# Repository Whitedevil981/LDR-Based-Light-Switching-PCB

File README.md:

# LDR-Based-Light-Switching-PCB
# Project Objective:
To design a light control system that automatically turns on a street light (or any light source) when it becomes dark and turns it off when there is sufficient daylight, using an LDR (Light Dependent Resistor) and basic electronic components.
# Working Principle:
The system is based on the light-sensing capability of an LDR. An LDR changes its resistance based on the intensity of light falling on it:

Bright light = low resistance

Darkness = high resistance

This change in resistance alters the voltage in a voltage divider circuit, which is used to switch a transistor. The transistor acts as an electronic switch to turn a relay or LED on or off.
# What the Basic PBC Circuit Includes:

LDR as light sensor

NPN Transistor 

LED/light bulb

Resistors 

Power supply (Battery)

# How It Works:
In daylight, the LDR has low resistance, so the transistor stays OFF → light/bulb is OFF.

At night or in darkness, LDR resistance increases, providing a base current to the transistor.

Transistor turns ON, activating the relay (or lighting up an LED/bulb).

The light remains ON until daylight is detected again.

# Applications:

Street lighting automation

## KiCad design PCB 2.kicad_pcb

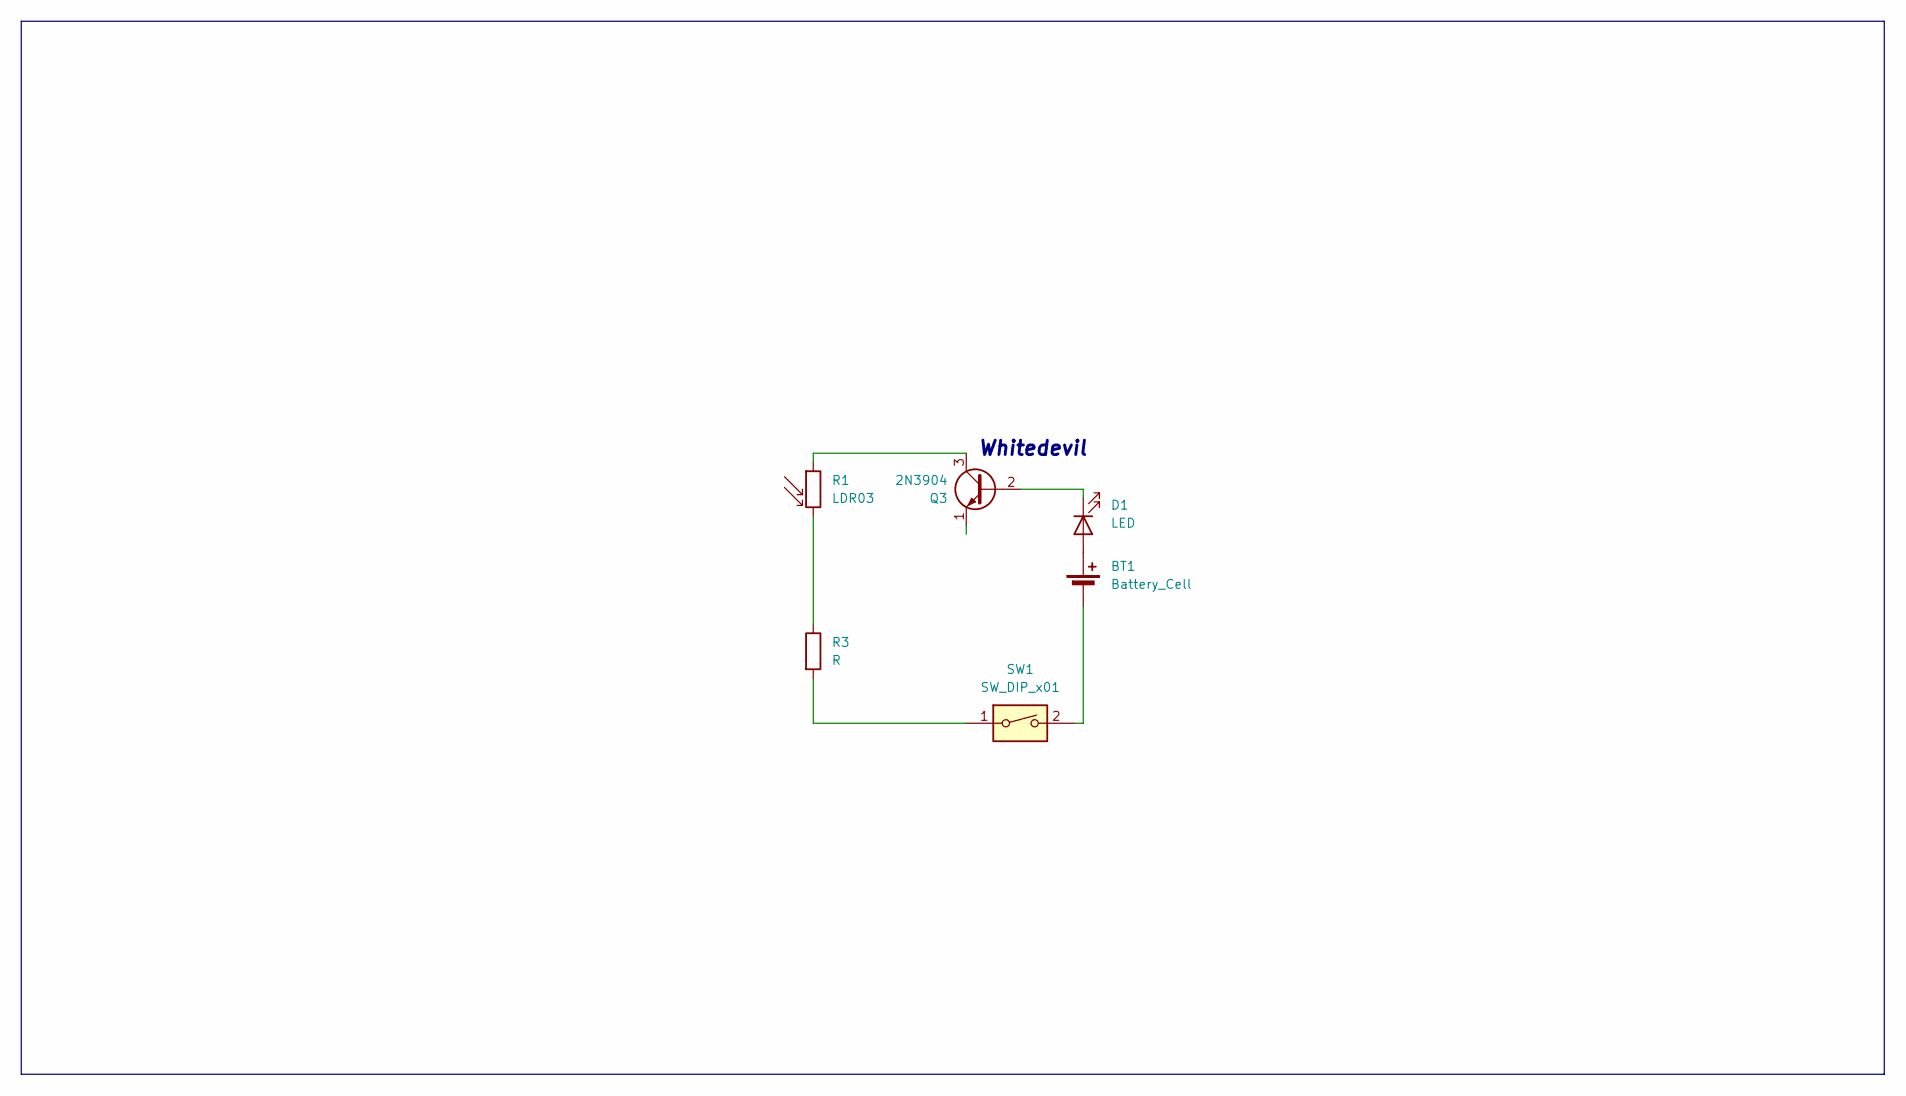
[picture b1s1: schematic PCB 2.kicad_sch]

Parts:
BT1: Battery_Cell; BatteryHolder_Keystone_3034_1x20mm
D1: LED; LED_D5.0mm
Q3: 2N3904; TO-92_Inline
R1: LDR03; R_LDR_7x6mm_P5.1mm_Vertical
R3: R; R_Axial_DIN0204_L3.6mm_D1.6mm_P5.08mm_Horizontal
SW1: SW_DIP_x01; SW_PUSH_6mm

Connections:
unnamed: BT1.1 (+), D1.2 (A)
unnamed: BT1.2 (-), SW1.2
unnamed: D1.1 (K), Q3.2 (B)
unnamed: Q3.3 (C), R1.1
unnamed: R1.2, R3.1
unnamed: R3.2, SW1.1

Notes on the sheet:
Whitedevil

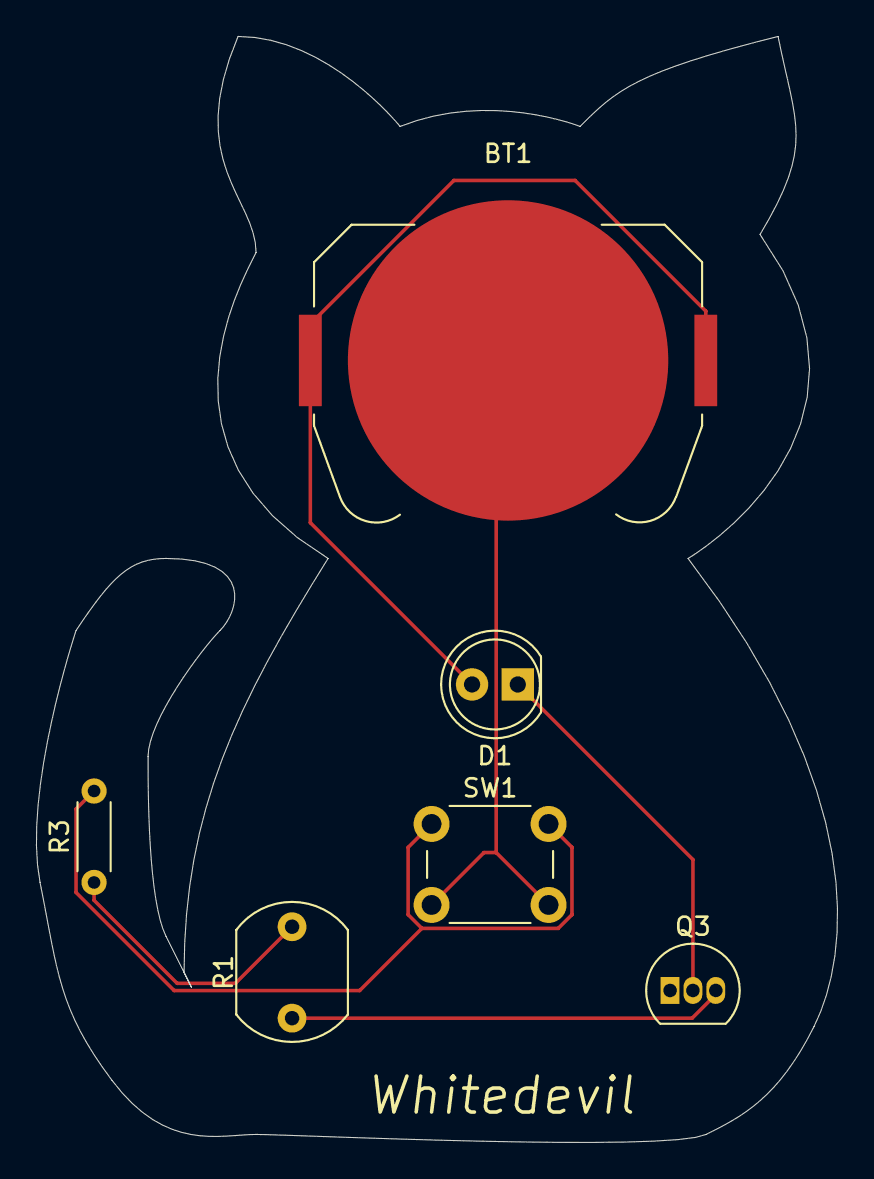
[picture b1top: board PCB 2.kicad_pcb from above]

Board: 2 copper layers, 44.5 x 61.4 mm, 6 parts (0 on the bottom side), 6 nets.
